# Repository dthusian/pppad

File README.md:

# pppad/2k

*Rapid trigger keypad for OSU!*
*Uses a rp2040 microcontroller with hall effect sensors*

* PCB files found in ./keypad
* Requires a magnet attached to the switch stem

## QMK Build instructions

Make example for this keyboard *(after setting up your build environment)*:

    make pppad/2k:default

Flashing example for this keyboard:

    make pppad/2k:default:flash

See the [build environment setup](https://docs.qmk.fm/#/getting_started_build_tools) and the [make instructions](https://docs.qmk.fm/#/getting_started_make_guide) for more information. Brand new to QMK? Start with our [Complete Newbs Guide](https://docs.qmk.fm/#/newbs).

## Bootloader

Enter the bootloader in 2 ways:

* **Bootmagic reset**: Hold down the key at (0,0) in the matrix and plug in the keyboard
* **Keycode in layout**: Press the key mapped to `QK_BOOT` if it is available

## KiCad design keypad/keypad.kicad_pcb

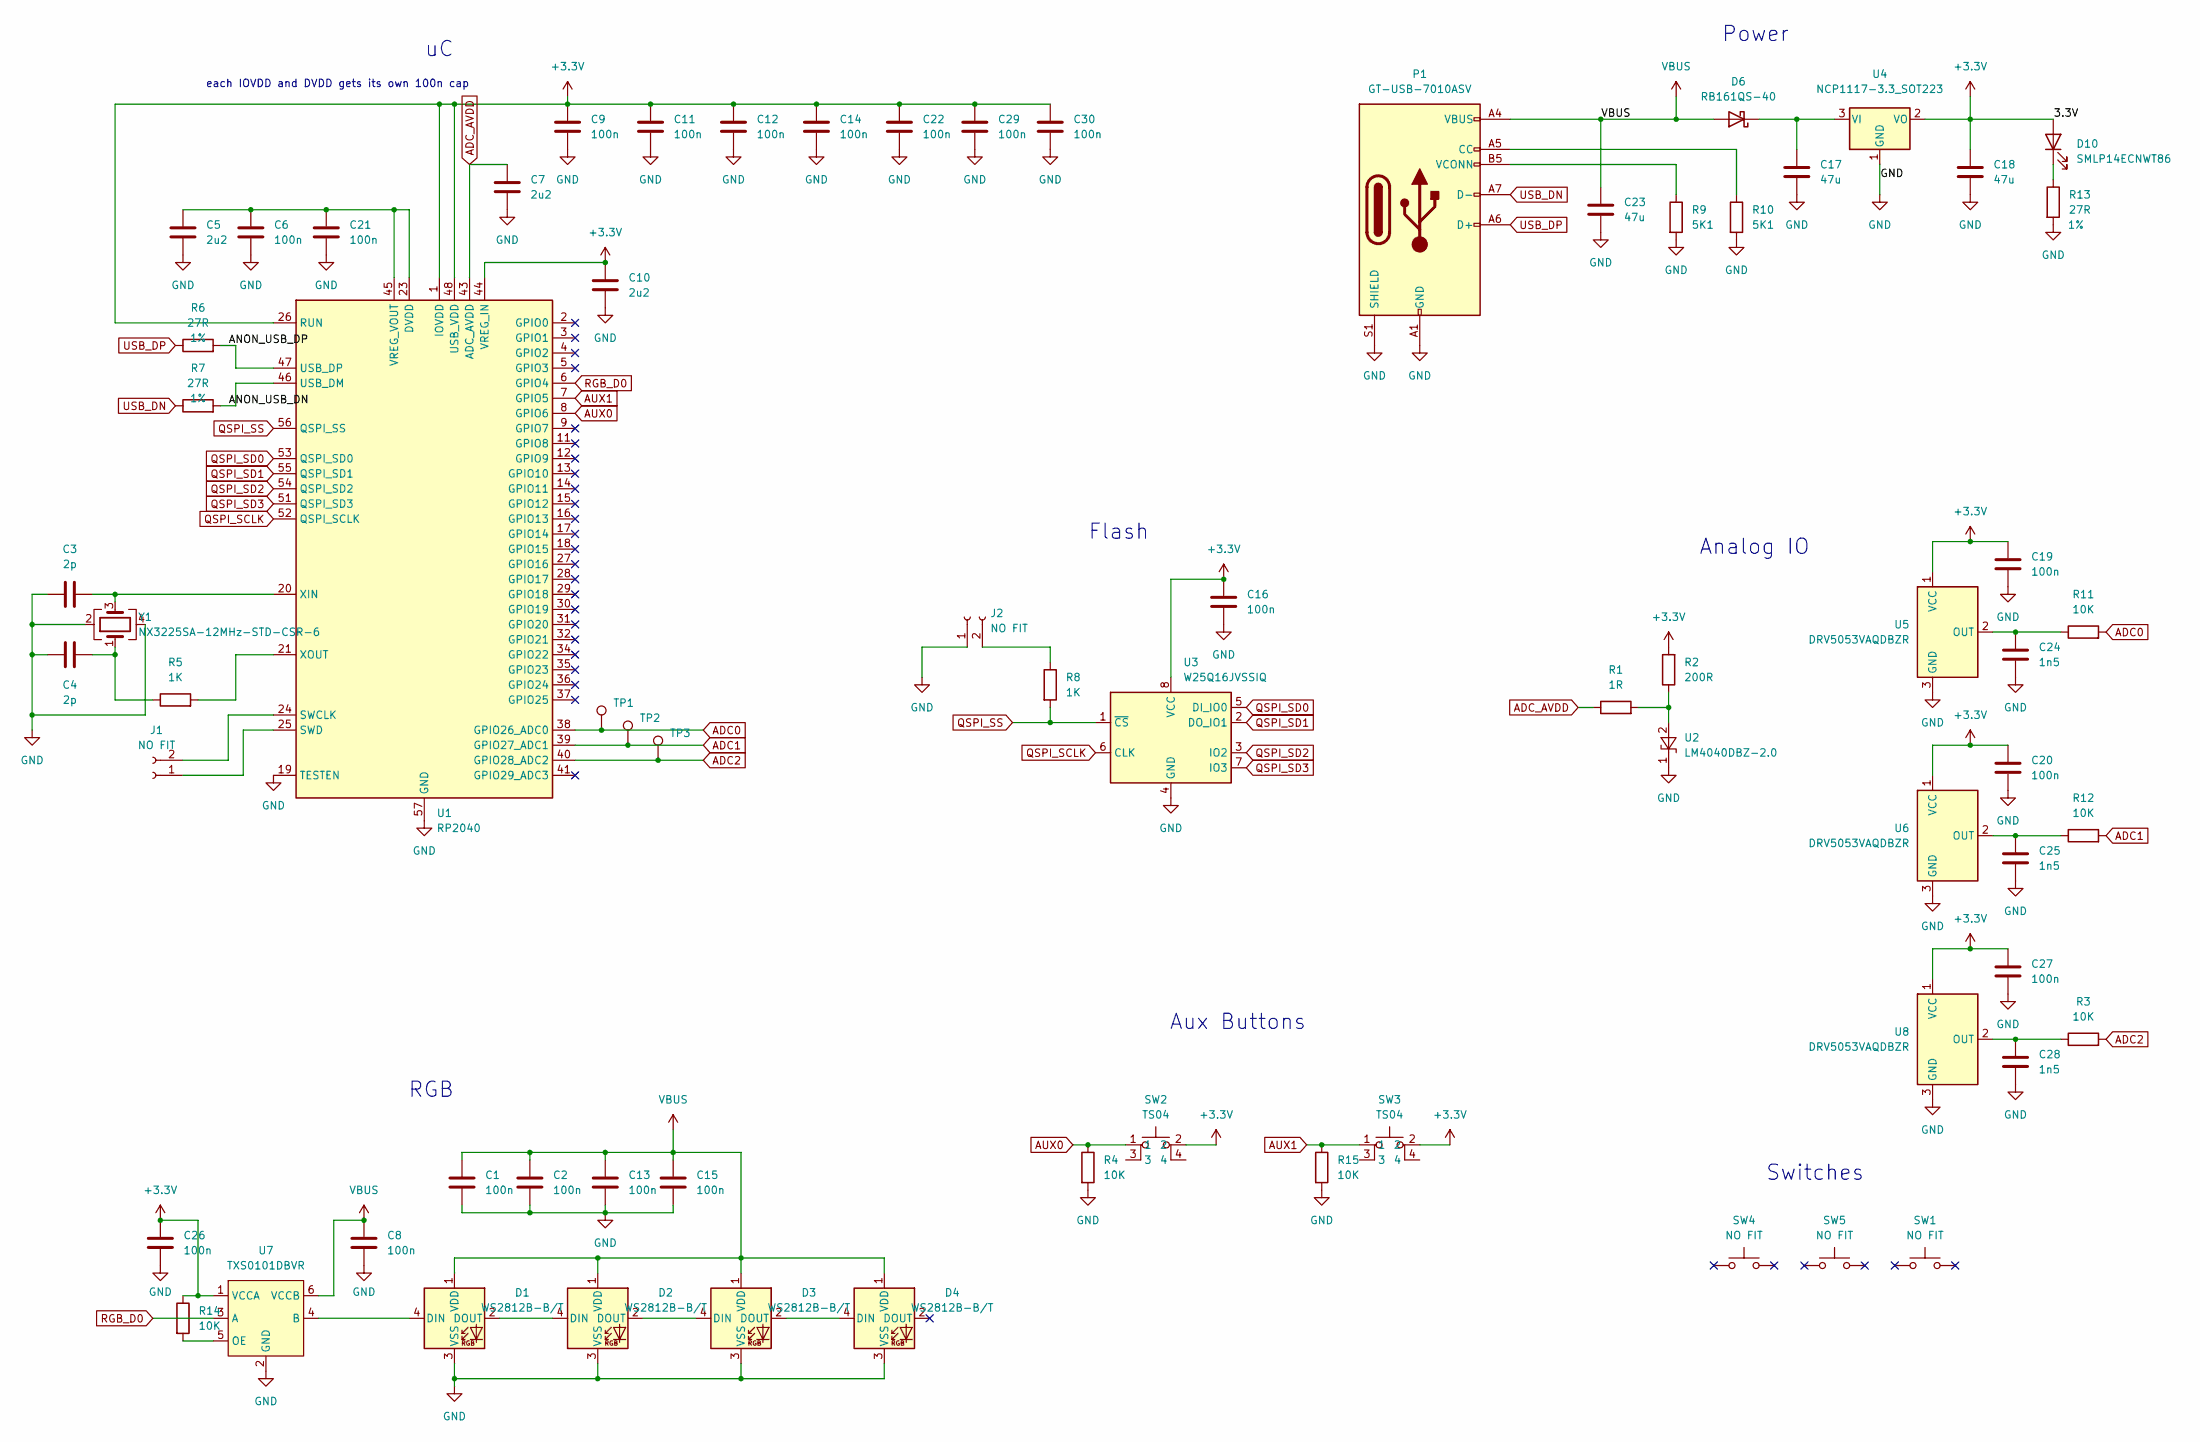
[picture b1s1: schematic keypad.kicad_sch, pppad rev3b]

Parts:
C1, C2, C6, C8, C9, C11, C12, C13, C14, C15, C16, C19, C20, C21, C22, C26, C27, C29, C30: 100n; C_0805_2012Metric
C3, C4: 2p; C_0805_2012Metric
C5, C7, C10: 2u2; C_0805_2012Metric
C17, C18, C23: 47u; C_0805_2012Metric
C24, C25, C28: 1n5; C_0805_2012Metric
D1, D2, D3, D4: WS2812B-B/T; LED_WS2812B_PLCC4_5.0x5.0mm_P3.2mm
D6: RB161QS-40; D_0402_1005Metric
D10: SMLP14ECNWT86; LED_0603_1608Metric
J1, J2: NO FIT; PinSocket_1x02_P2.00mm_Vertical
P1: GT-USB-7010ASV; USB_C_Receptacle_G-Switch_GT-USB-7010ASV
R1: 1R; R_0805_2012Metric
R2: 200R; R_0805_2012Metric
R3, R4, R11, R12, R14, R15: 10K; R_0805_2012Metric
R5: 1K; R_0805_2012Metric; Tolerance 1%
R6, R7, R13: 27R; R_0805_2012Metric; Tolerance 1%
R8: 1K; R_0805_2012Metric
R9, R10: 5K1; R_0805_2012Metric
SW1, SW4, SW5: NO FIT; SW_Cherry_MX_1.00u_PCB
SW2, SW3: TS04
TP1, TP2, TP3: NO FIT; TestPoint_Pad_1.5x1.5mm
U1: RP2040; QFN-56-1EP_7x7mm_P0.4mm_EP3.2x3.2mm
U2: LM4040DBZ-2.0; SOT-23
U3: W25Q16JVSSIQ; SOIC-8_5.23x5.23mm_P1.27mm
U4: NCP1117-3.3_SOT223; SOT-223-3_TabPin2
U5, U6, U8: DRV5053VAQDBZR; SOT-23
U7: TXS0101DBVR; SOT-23-6
Y1: NX3225SA-12MHz-STD-CSR-6; Crystal_SMD_NX3225SA

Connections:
+3.3V: C9.1, C10.1, C11.1, C12.1, C14.1, C16.1, C18.1, C19.1, C20.1, C22.1, C26.1, C27.1, C29.1, C30.1, D10.2 (A), R2.2, R14.1, SW2.2, SW3.2, U1.1 (IOVDD), U1.10 (IOVDD), U1.22 (IOVDD), U1.26 (RUN), U1.33 (IOVDD), U1.42 (IOVDD), U1.44 (VREG_IN), U1.48 (USB_VDD), U1.49 (IOVDD), U3.8 (VCC), U4.2 (VO), U5.1 (VCC), U6.1 (VCC), U7.1 (VCCA), U8.1 (VCC)
/ANON_USB_DN: R7.2, U1.46 (USB_DM)
/ANON_USB_DP: R6.2, U1.47 (USB_DP)
ADC0: R11.2, TP1.1, U1.38 (GPIO26_ADC0)
ADC1: R12.2, TP2.1, U1.39 (GPIO27_ADC1)
ADC2: R3.2, TP3.1, U1.40 (GPIO28_ADC2)
ADC_AVDD: C7.1, R1.1, U1.43 (ADC_AVDD)
AUX0: R4.1, SW2.1, U1.8 (GPIO6)
AUX1: R15.1, SW3.1, U1.7 (GPIO5)
GND: C1.2, C2.2, C3.1, C4.1, C5.2, C6.2, C7.2, C8.2, C9.2, C10.2, C11.2, C12.2, C13.2, C14.2, C15.2, C16.2, C17.2, C18.2, C19.2, C20.2, C21.2, C22.2, C23.2, C24.2, C25.2, C26.2, C27.2, C28.2, C29.2, C30.2, D1.3 (VSS), D2.3 (VSS), D3.3 (VSS), D4.3 (VSS), J2.1, P1.A1 (GND), P1.A12 (GND), P1.B1 (GND), P1.B12 (GND), P1.S1 (SHIELD), R4.2, R9.2, R10.2, R13.2, R15.2, U1.19 (TESTEN), U1.57 (GND), U2.1 (K), U3.4 (GND), U4.1 (GND), U5.3 (GND), U6.3 (GND), U7.2 (GND), U8.3 (GND), Y1.2, Y1.4
unnamed: C3.2, U1.20 (XIN), Y1.3
unnamed: C4.2, R5.1, Y1.1
unnamed: C17.1, D6.1 (K), U4.3 (VI)
unnamed: C5.1, C6.1, C21.1, U1.23 (DVDD), U1.45 (VREG_VOUT), U1.50 (DVDD)
unnamed: C24.1, R11.1, U5.2 (OUT)
unnamed: C25.1, R12.1, U6.2 (OUT)
unnamed: C28.1, R3.1, U8.2 (OUT)
unnamed: D1.2 (DOUT), D2.4 (DIN)
unnamed: D1.4 (DIN), U7.4 (B)
unnamed: D2.2 (DOUT), D3.4 (DIN)
unnamed: D3.2 (DOUT), D4.4 (DIN)
unnamed: D10.1 (K), R13.1
unnamed: J1.1, U1.25 (SWD)
unnamed: J1.2, U1.24 (SWCLK)
unnamed: J2.2, R8.1
unnamed: P1.A5 (CC), R10.1
unnamed: P1.B5 (VCONN), R9.1
unnamed: R1.2, R2.1, U2.2 (A)
unnamed: R5.2, U1.21 (XOUT)
unnamed: R14.2, U7.5 (OE)
QSPI_SCLK: U1.52 (QSPI_SCLK), U3.6 (CLK)
QSPI_SD0: U1.53 (QSPI_SD0), U3.5 (DI_IO0)
QSPI_SD1: U1.55 (QSPI_SD1), U3.2 (DO_IO1)
QSPI_SD2: U1.54 (QSPI_SD2), U3.3 (IO2)
QSPI_SD3: U1.51 (QSPI_SD3), U3.7 (IO3)
QSPI_SS: R8.2, U1.56 (QSPI_SS), U3.1 (~CS)
RGB_D0: U1.6 (GPIO4), U7.3 (A)
USB_DN: P1.A7 (D-), P1.B7 (D-), R7.1
USB_DP: P1.A6 (D+), P1.B6 (D+), R6.1
VBUS: C1.1, C2.1, C8.1, C13.1, C15.1, C23.1, D1.1 (VDD), D2.1 (VDD), D3.1 (VDD), D4.1 (VDD), D6.2 (A), P1.A4 (VBUS), P1.A9 (VBUS), P1.B4 (VBUS), P1.B9 (VBUS), U7.6 (VCCB)

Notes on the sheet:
Power
Flash
Switches
Analog IO
Aux Buttons
each IOVDD and DVDD gets its own 100n cap
RGB

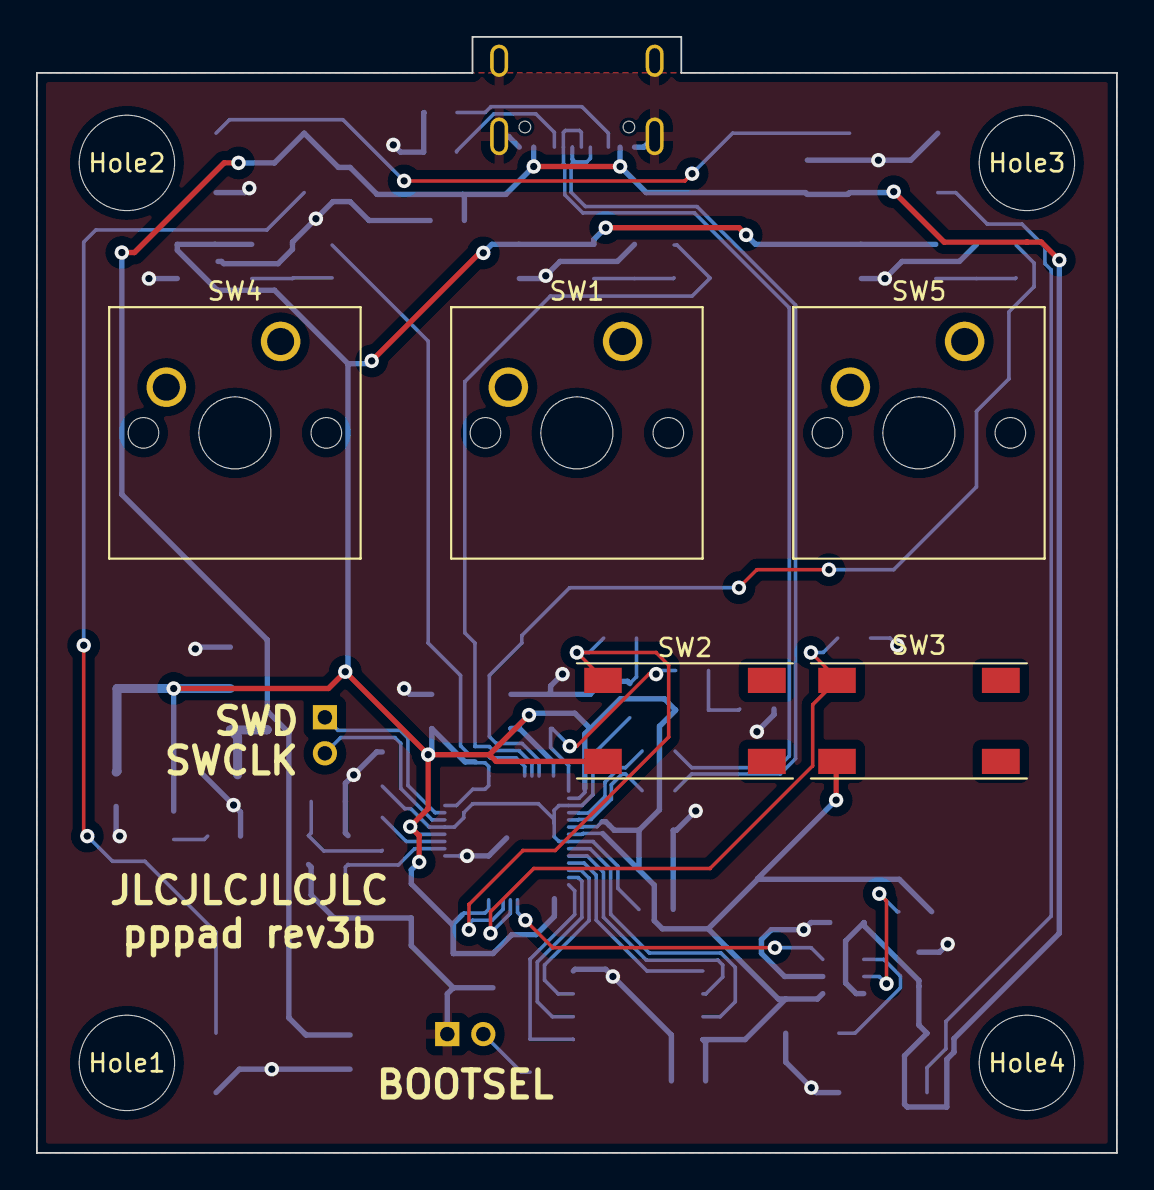
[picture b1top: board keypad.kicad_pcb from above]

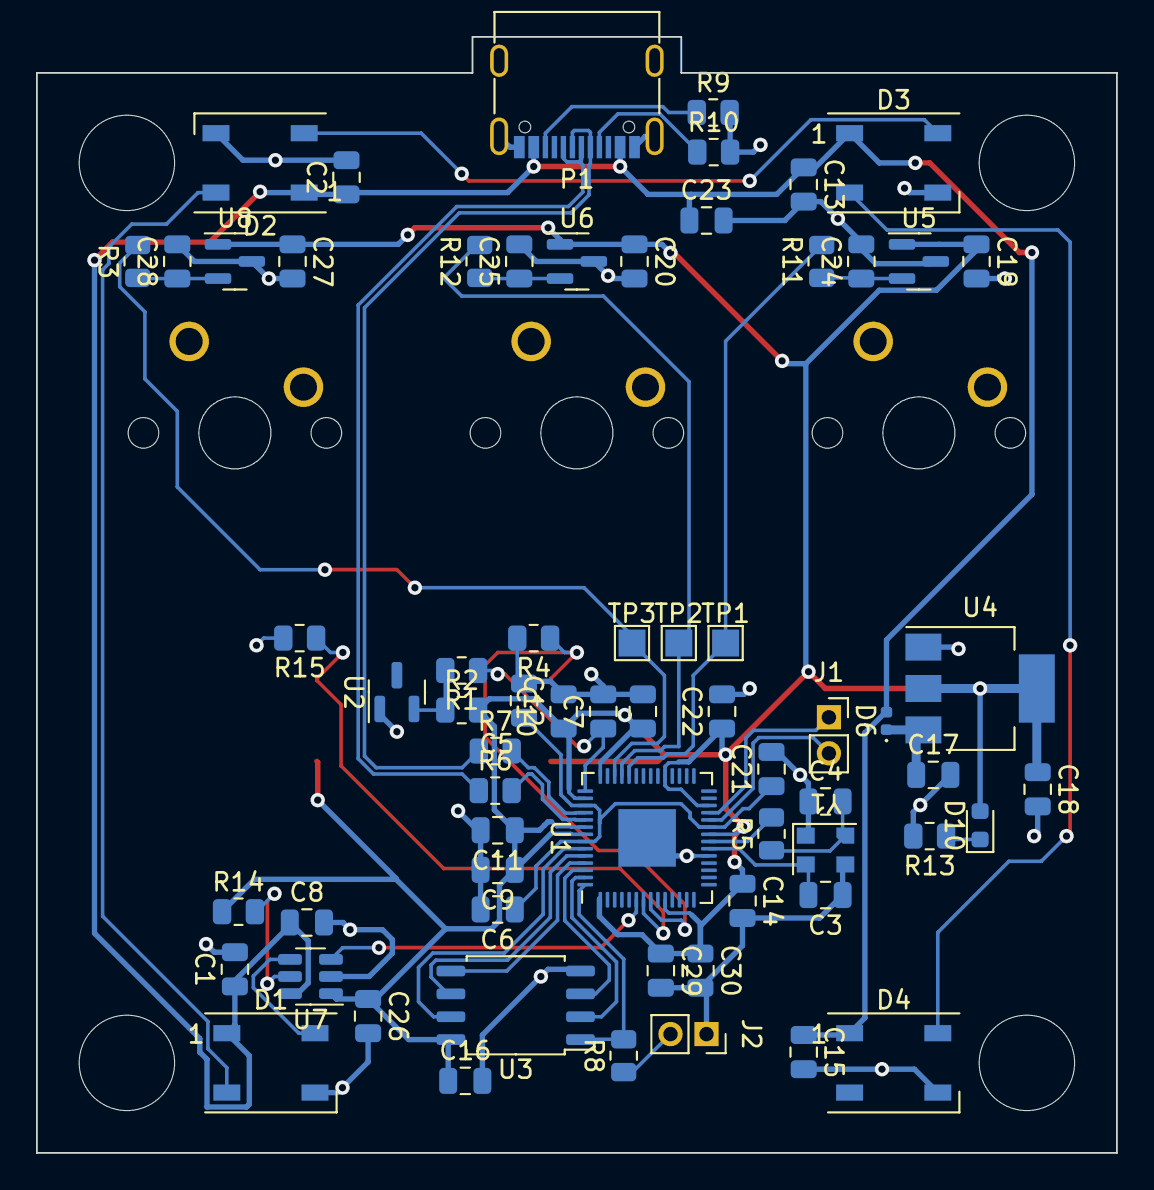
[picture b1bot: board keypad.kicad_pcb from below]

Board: 2 copper layers, 60.0 x 62.0 mm, 75 parts (66 on the bottom side), 40 nets.

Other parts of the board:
Hole1, Hole2, Hole3, Hole4: MountingHole_5.3mm_M5

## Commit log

2023-04-08 velcome to os
2023-04-10 Finish RGB and start power
2023-04-11 finish placing everything
2023-04-11 fix all the disconnected GND problems
2023-04-11 Rewire RGB to add space for screwholes
2023-04-11 Re-spec USB-C and power diode
2023-04-15 Minor updates, prep for fab
2023-04-17 fix mistakes because i am big dum
2023-04-17 realign everything
2023-04-17 move switches slighltly
2023-04-17 Size increase to accomodate for mechanical
2023-04-19 fix up stuff for fab
2023-05-02 Make alterations for rev3
2023-05-03 ditch rev3a for rev3b
2023-05-04 initial placements for rev3b
2023-05-05 finish rev3b
2023-05-05 add helpful silkscreening
2025-09-10 add fw
2025-09-10 add readme
